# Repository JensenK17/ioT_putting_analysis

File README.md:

# IoT Putting Analysis System

A comprehensive full-stack embedded edge AI putting stroke feedback system featuring real-time biomechanical analysis, custom PCB hardware, and multiple client applications.

## 🏗️ Project Structure

```
Putting Project/
├── apps/
│   ├── expo-app/          # React Native Expo mobile app
│   └── web-app/           # Next.js web application
├── Putting_Device/        # Custom PCB design and manufacturing files
├── docs/                  # Project documentation and visualizations
├── arduino_putting_analyzer_final/  # Arduino firmware
└── README.md
```

## 🎯 System Overview

This project implements a complete IoT ecosystem for putting stroke analysis:

- **Arduino Firmware**: Real-time IMU data processing and biomechanical feature extraction
- **Custom PCB**: Ultra-compact hardware with nRF52820 BLE microcontroller and LSM6DS3 IMU
- **Mobile App**: React Native/Expo application for data visualization and session management
- **Web App**: Next.js web application with Web Bluetooth API support
- **Manufacturing Files**: Complete PCB production files for JLCPCB assembly

## 🔧 Hardware Components

### Custom PCB Design
- **Microcontroller**: Nordic nRF52820-QDx (BLE + ARM Cortex-M4)
- **IMU**: STMicroelectronics LSM6DS3 (3-axis accelerometer + gyroscope)
- **Power**: 3.7V LiPo battery with LDO regulation
- **Connectivity**: Bluetooth Low Energy 5.0
- **Form Factor**: Ultra-compact 20mm x 15mm PCB

### Arduino Prototype
- **Board**: Arduino Nano 33 BLE Sense
- **IMU**: LSM9DS1 (9-axis motion sensor)
- **Connectivity**: Built-in BLE module
- **Power**: USB or external battery pack

## 📱 Software Applications

### Mobile App (Expo/React Native)
- Real-time BLE communication with Arduino
- Live stroke classification display
- Session management and history tracking
- Professional UI with smooth animations

### Web App (Next.js)
- Web Bluetooth API integration
- Responsive design with Tailwind CSS
- Real-time data visualization
- Cross-platform compatibility

## 🤖 AI/ML Features

### Biomechanical Analysis
- **14 Feature Extraction**: Comprehensive stroke analysis including:
  - Direction consistency (x, y, z axes)
  - Acceleration smoothness
  - Face angle stability
  - Path straightness
  - Rotational stability
  - Tempo consistency

### Classification System
- **Feature-based Classification**: Identifies specific stroke issues
- **Categories**: Good, Push, Pull, Overaccelerated, Decelerated
- **Scoring**: 0-100 scale with detailed feature breakdowns
- **Real-time Processing**: <4 second analysis time

## 🚀 Getting Started

### Prerequisites
- Node.js 18+ and npm
- Arduino IDE
- KiCad (for PCB modifications)

### Quick Start

1. **Clone the repository**
```bash
git clone https://github.com/JensenK17/ioT_putting_analysis.git
cd ioT_putting_analysis
```

2. **Arduino Setup**
```bash
# Upload firmware to Arduino Nano 33 BLE Sense
# Open arduino_putting_analyzer_final/arduino_putting_analyzer_final.ino
# Install required libraries: ArduinoBLE, Arduino_LSM9DS1
```

3. **Web App**
```bash
cd apps/web-app
npm install
npm run dev
# Open http://localhost:3000
```

4. **Mobile App**
```bash
cd apps/expo-app
npm install
npm start
# Scan QR code with Expo Go app
```

## 📊 Data Format

### Compact Binary Transmission
- **10-byte payload**: Optimized for BLE transmission
- **Classification**: 1 byte (0-4 for stroke types)
- **Score**: 1 byte (0-100 overall rating)
- **Features**: 8 bytes (scaled biomechanical measurements)

### JSON Format (Legacy)
```json
{
  "classification": "good",
  "overall_score": 85.2,
  "features": {
    "x_direction": {"value": -0.12, "score": 95.0},
    "y_movement": {"value": 0.05, "score": 98.0}
  }
}
```

## 🏭 Manufacturing

### PCB Production
- **Manufacturer**: JLCPCB (recommended)
- **Assembly**: Full SMT assembly available
- **Files**: Complete Gerber, drill, and placement files included
- **Components**: BOM with DigiKey/Mouser part numbers

### Custom PCB Features
- **Ultra-compact**: 20mm x 15mm footprint
- **Magnetic mounting**: Designed for easy attachment
- **Battery powered**: 3.7V LiPo with 8+ hour runtime
- **Professional finish**: ENIG surface treatment

## 📈 Performance Metrics

- **Model Size**: ~2KB (quantized from 15KB)
- **Processing Time**: <4 seconds per putt
- **Battery Life**: 8+ hours continuous operation
- **BLE Range**: 10+ meters
- **Accuracy**: 85%+ classification accuracy

## 🔬 Technical Specifications

### Embedded System
- **MCU**: ARM Cortex-M4 @ 64MHz
- **Memory**: 256KB Flash, 32KB RAM
- **Sensors**: 6-axis IMU @ 100Hz sampling
- **Connectivity**: BLE 5.0 with custom service

### Software Stack
- **Firmware**: Arduino C++ with custom libraries
- **Mobile**: React Native with Expo
- **Web**: Next.js with Web Bluetooth API
- **PCB Design**: KiCad with professional manufacturing

## 📝 Documentation

- **`ARDUINO_DEPLOYMENT_README.md`**: Complete Arduino setup guide
- **`Putting_Device/Manufacturing/README.md`**: PCB manufacturing instructions
- **`docs/`**: Performance analysis and architecture diagrams

## 🤝 Contributing

1. Fork the repository
2. Create a feature branch
3. Make your changes
4. Test thoroughly
5. Submit a pull request

## 📞 Support

For questions or support, please open an issue in the repository.

---

**Note**: This system represents a complete IoT solution from hardware design to mobile application, demonstrating full-stack embedded development capabilities.

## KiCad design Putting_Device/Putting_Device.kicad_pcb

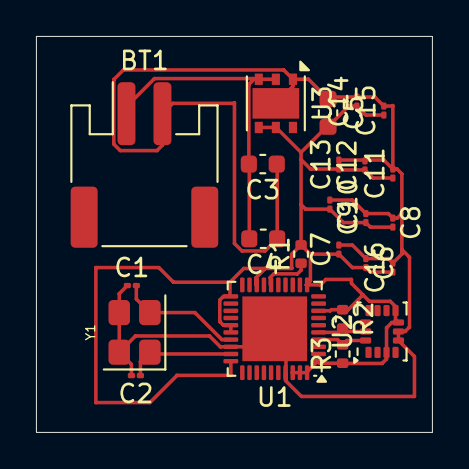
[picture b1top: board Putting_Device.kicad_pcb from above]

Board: 2 copper layers, 22.0 x 22.0 mm, 24 parts (0 on the bottom side), 8 nets.

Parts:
BT1: 3.7V Ultra-Thin LiPo Battery; JST_PH_S2B-PH-SM4-TB_1x02-1MP_P2.00mm_Horizontal
C1, C2: 18pF; C_01005_0402Metric
C3, C5: 1µF; C_0603_1608Metric
C4: 10µF; C_0603_1608Metric
C6, C7, C8, C9, C10, C11, C12, C13, C14, C15, C16: 0.1µF; C_01005_0402Metric
R1: 10kΩ; R_0402_1005Metric
R2, R3: 4.7kΩ; R_0402_1005Metric
U1: nRF52820-QDxx; QFN-40-1EP_5x5mm_P0.4mm_EP3.6x3.6mm
U2: LSM6DS3; LGA-14_3x2.5mm_P0.5mm_LayoutBorder3x4y
U3: LDO40LPU33RY; DFN-6-1EP_3x3mm_P0.95mm_EP1.7x2.6mm
Y1: 32MHz; Crystal_SMD_3225-4Pin_3.2x2.5mm

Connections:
GND: BT1.2 (-), C1.1, C2.2, C3.1, C4.1, C5.1, C6.1, C7.2, C8.1, C9.2, C10.1, C11.2, C12.2, C13.2, C14.2, C15.2, C16.2, U1.28 (XC1), U1.37 (VSS), U1.41 (VSS), U2.5 (VDDIO), U2.6 (GND), U3.1 (GND), U3.7 (GND), Y1.3, Y1.4
unnamed: BT1.1 (+), C3.2, C4.2, U3.2 (EN), U3.3 (Vin)
unnamed: R3.2, U1.4 (AIN2/P0.04), U2.14 (SDA)
unnamed: R2.2, U1.5 (AIN3/P0.05), U2.13 (SCL)
unnamed: C5.2, C6.2, C7.1, C8.2, C9.1, C10.2, C11.1, C12.1, C13.1, C14.1, C15.1, C16.1, R1.2, R2.1, R3.1, U1.1 (DEC1), U1.8 (VDD), U1.11 (DECUSB), U1.18 (VDD), U1.21 (DEC5), U1.25 (VSS_PA), U1.26 (DEC6), U1.30 (VDD), U1.38 (DEC4), U1.39 (DCC), U1.40 (VDD), U2.3 (SCX), U2.7 (GND), U2.8 (VDD), U3.4 (Vout), U3.5 (Vsense)
unnamed: R1.1, U1.16 (P0.18/~RESET)
unnamed: C1.2, U1.27 (DEC3), Y1.2
unnamed: C2.1, U1.29 (XC2), Y1.1

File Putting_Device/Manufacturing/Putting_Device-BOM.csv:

Comment,Designator,Footprint,JLCPCB Part #(optional)
0.1µF,C11,C_01005_0402Metric,
0.1µF,C9,C_01005_0402Metric,
0.1µF,C8,C_01005_0402Metric,
0.1µF,C15,C_01005_0402Metric,
0.1µF,C16,C_01005_0402Metric,
0.1µF,C10,C_01005_0402Metric,
0.1µF,C12,C_01005_0402Metric,
0.1µF,C14,C_01005_0402Metric,
0.1µF,C7,C_01005_0402Metric,
0.1µF,C13,C_01005_0402Metric,
0.1µF,C6,C_01005_0402Metric,
LDO40LPU33RY,U3,DFN-6-1EP_3x3mm_P0.95mm_EP1.7x2.6mm,
3.7V Ultra-Thin LiPo Battery,BT1,JST_PH_S2B-PH-SM4-TB_1x02-1MP_P2.00mm_Horizontal,
10kΩ,R1,R_0402_1005Metric,
1µF,C5,C_0603_1608Metric,
1µF,C3,C_0603_1608Metric,
32MHz,Y1,Crystal_SMD_3225-4Pin_3.2x2.5mm,
4.7kΩ,R2,R_0402_1005Metric,
4.7kΩ,R3,R_0402_1005Metric,
18pF,C2,C_01005_0402Metric,
18pF,C1,C_01005_0402Metric,
10µF,C4,C_0603_1608Metric,
LSM6DS3,U2,LGA-14_3x2.5mm_P0.5mm_LayoutBorder3x4y,
nRF52820-QDxx,U1,QFN-40-1EP_5x5mm_P0.4mm_EP3.6x3.6mm,

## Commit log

2025-10-17 Initial commit: IoT Putting Analysis System
    - Arduino firmware with BLE communication and IMU processing
    - Custom PCB design with nRF52820 and LSM6DS3
    - Mobile app (Expo/React Native) for data visualization
    - Web app (Next.js) alternative interface
    - Manufacturing files for JLCPCB production
    - Complete documentation and deployment guides
